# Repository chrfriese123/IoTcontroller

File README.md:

# ESP8266 based controller for smart home applications
## Introduction
The target is to setup a versatile smart home system. Home Assistant (www.home-assistant.io) running on a Raspberry Pi is used as open-source platform to integrate various devices from multiple brands. Especially to control lights and covers a system should comply with four requirements: 
- can be directly connected to the wall switches (limited size)
- is not linked to a specific supplier (open source)
- has direct connection to the host controller without the need of a bridge (Wifi)
- has low cost

As a solution a system based on an ESP8266 chip operated with Tasmota (tasmota.github.io) seems suitable. 

## Implementation
The schematic and layout of the PCB was implemented with the free version of KiCAD. The key elements are inspired by proven designs and combined in a minimalistic way on the PCB.

### Power supply
For the power supply, two step-down converters are used. The first one to convert from 230VAC to 5VDC. This is mainly used to operate the relays. The second conversion is by a simple LDO from 5VDC to 3.3VDC to operate the ESP8266.

### ESP8266 contoller
As controller an ESP8266 module was used to operate up to two relays, enable two external switches as input and a I2C communication to external devices.

For the operation and programming of the ESP8266 certain pins need to be pulled high. Two miniaturized switches are included to reset the device or get into programming mode.

### Relays
Two relay channels are implemented to allow an operation of one cover or two lights with the system. As option, an LED can be activated to indicate the state of the relay.

### Layout
The layout is defined by the used wall switch program. Two screw holes need to be considered, front size has a reduced size and limited height.

To reduce the risk, high voltage line are placed on the backside, covered by components. Low voltage and signal lines are placed as much as possible of the frontside. 

### ESP8266 contoller
As controller an ESP8266 module was used to operate up to two relays, enable two external switches as input and a I2C communication to external devices.

For the operation and programming of the ESP8266 certain pins need to be pulled high. Two miniaturized switches are included to reset the device or get into programming mode.

### Relays
Two relay channels are implemented to allow an operation of one cover or two lights with the system. As option, an LED can be activated to indicate the state of the relay.

### Layout
The layout is defined by the used wall switch program. Two screw holes need to be considered, front size has a reduced size and limited height.
To reduce the risk, high voltage line are placed on the backside, covered by components. Low voltage and signal lines are placed as much as possible of the frontside. 

### Firmware
To operate the ESP system, the open-source firmware Tasmota is used (https://tasmota.github.io/docs/). For the majority of the controllers the standard firmware is suitable. Although some cases need a dedicated version to enable operation of RGB LED stripes, read specific I2C sensors or read the power & water meters.

### Preparation
The bare PCB is produced by a Chinese manufacturer. Assembly is done manually, first the SMD components and the ESP8266 module. Then a system check and programming is performed. Finally, the through hole components are soldered.

## Summary
Currently 24 of theses IoT controller are installed and running as
- Cover switches
- Light switches (bulbs and RGB LEDs)
- 3D printer controller
- Power & water metering
- Valve controller for gardening
- Environmental sensors
  
The overall failure rate of the system is low and not except for one ESP8266 module breakdown not linked to the design. The cost of one module is about 10€. To conclude, the initial targets are fulfilled, and the system is constantly extended.

### Next steps
As an improved version the transition to ESP32 would be helpful to increase the number of available GPIOs. Another limitation is that the relays can only handle 7A max current, which might be critical for some use-cases

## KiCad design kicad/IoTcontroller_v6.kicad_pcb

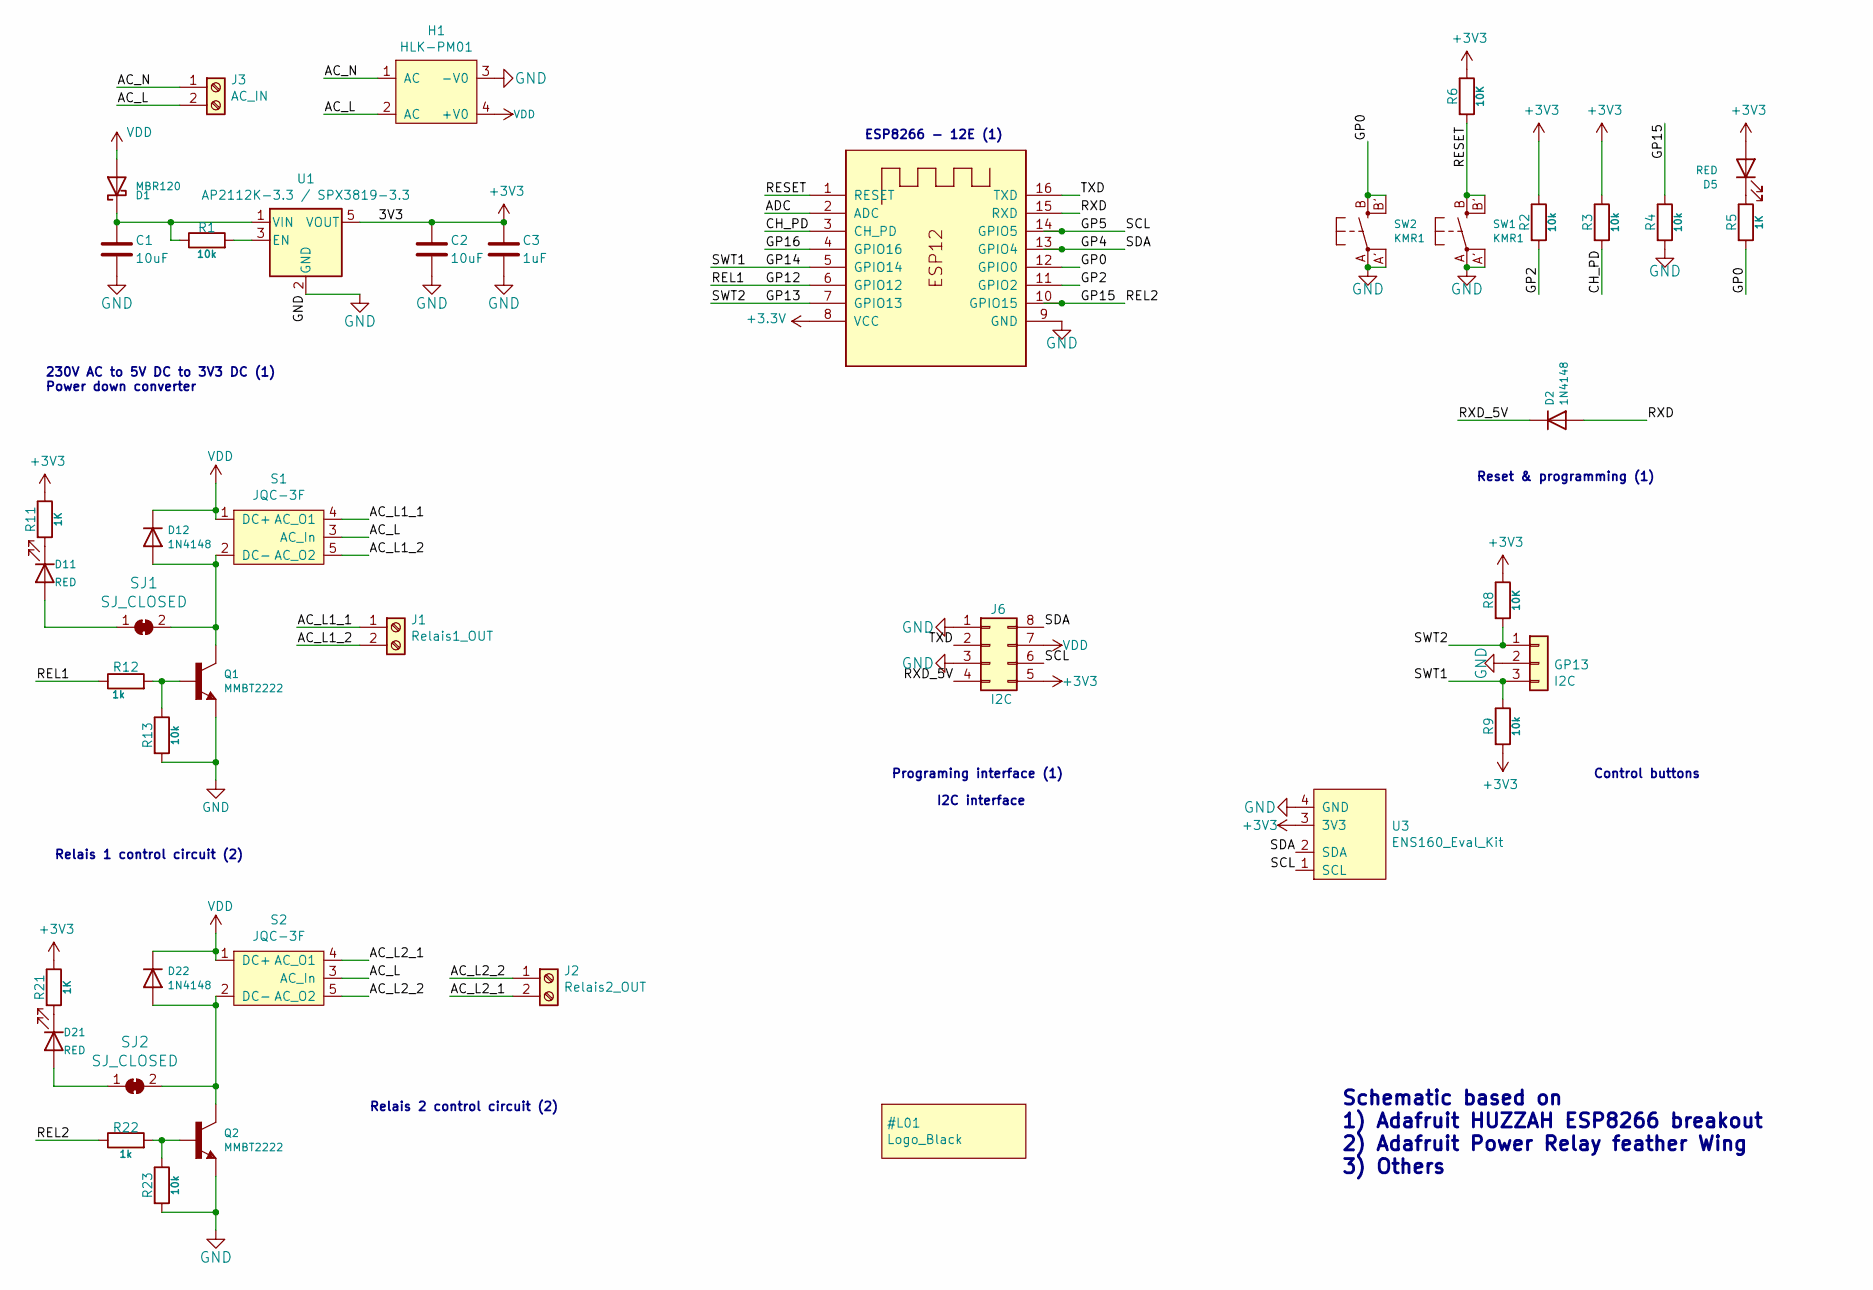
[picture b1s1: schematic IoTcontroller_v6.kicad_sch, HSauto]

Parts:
C1, C2: 10uF; C_0805_2012Metric
C3: 1uF; C_0805_2012Metric
D1: MBR120; D_SOD-123
D2, D12, D22: 1N4148; D_SOD-323
D5, D11, D21: RED; LED_0805_2012Metric
GP13: I2C; PinHeader_1x03_P2.54mm_Vertical
H1: HLK-PM01
J1: Relais1_OUT; PTSA1,5-2-3,5-Z
J2: Relais2_OUT; PTSA1,5-2-3,5-Z
J3: AC_IN; PTSA1,5-2-3,5-Z
J6: I2C; PinHeader_2x04_P2.54mm_Vertical
Q1, Q2: MMBT2222; SOT-23
R1, R2, R3, R4, R9, R13, R23: 10k; R_0805_2012Metric
R5, R11, R21: 1K; R_0805_2012Metric
R6, R8: 10K; R_0805_2012Metric
R12, R22: 1k; R_0805_2012Metric
S1, S2: JQC-3F
SJ1, SJ2: SJ_CLOSED; SolderJumper-2_P1.3mm_Bridged_RoundedPad1.0x1.5mm
SW1, SW2: KMR1; BTN_KMR2_4.6X2.8
U1: AP2112K-3.3 / SPX3819-3.3; SOT-23-5
U3: ENS160_Eval_Kit; ScioSense_ENS16x_EvalKit
X1: ESP-12

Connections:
/AC_L: H1.2 (AC), J3.2, S1.3 (AC_In), S2.3 (AC_In)
/AC_L1_1: J1.1, S1.4 (AC_O1)
/AC_L1_2: J1.2, S1.5 (AC_O2)
/AC_L2_1: J2.2, S2.4 (AC_O1)
/AC_L2_2: J2.1, S2.5 (AC_O2)
/AC_N: H1.1 (AC), J3.1
/ADC: X1.2 (ADC)
/CH_PD: R3.2, X1.3 (CH_PD)
/GP0: R5.2, SW2.B (S), SW2.B' (S1), X1.12 (GPIO0)
/GP2: R2.2, X1.11 (GPIO2)
/GP4: J6.8, U3.2 (SDA), X1.13 (GPIO4)
/GP5: J6.6, U3.1 (SCL), X1.14 (GPIO5)
/GP12: R12.1, X1.6 (GPIO12)
/GP13: GP13.1, R8.2, X1.7 (GPIO13)
/GP14: GP13.3, R9.1, X1.5 (GPIO14)
/GP15: R4.1, R22.1, X1.10 (GPIO15)
/GP16: X1.4 (GPIO16)
/RESET: R6.2, SW1.B (S), SW1.B' (S1), X1.1 (RESET)
/RXD: D2.2 (A), X1.15 (RXD)
/RXD_5V: D2.1 (K), J6.4
/TXD: J6.2, X1.16 (TXD)
GND: C1.2, C2.2, C3.2, GP13.2, H1.3 (-V0), J6.1, J6.3, Q1.2 (E), Q2.2 (E), R4.2, R13.2, R23.2, SW1.A, SW1.A' (P1), SW2.A, SW2.A' (P1), U1.2 (GND), U3.4 (GND), X1.9 (GND)
unnamed: C1.1, D1.1 (K), R1.1, U1.1 (VIN)
unnamed: D5.1 (K), R5.1
unnamed: D11.2 (A), SJ1.1 (A)
unnamed: D11.1 (K), R11.2
unnamed: D12.2 (A), Q1.3 (C), S1.2 (DC-), SJ1.2 (B)
unnamed: D21.2 (A), SJ2.1 (A)
unnamed: D21.1 (K), R21.2
unnamed: D22.2 (A), Q2.3 (C), S2.2 (DC-), SJ2.2 (B)
unnamed: Q1.1 (B), R12.2, R13.1
unnamed: Q2.1 (B), R22.2, R23.1
unnamed: R1.2, U1.3 (EN)
VDD: D1.2 (A), D12.1 (K), D22.1 (K), H1.4 (+V0), J6.7, S1.1 (DC+), S2.1 (DC+)

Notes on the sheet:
Control buttons
230V AC to 5V DC to 3V3 DC (1) Power down converter
Relais 2 control circuit (2)
Relais 1 control circuit (2)
ESP8266 - 12E (1)
I2C interface
Reset & programming (1)
Programing interface (1)
Schematic based on 1) Adafruit HUZZAH ESP8266 breakout 2) Adafruit Power Relay feather Wing 3) Others

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
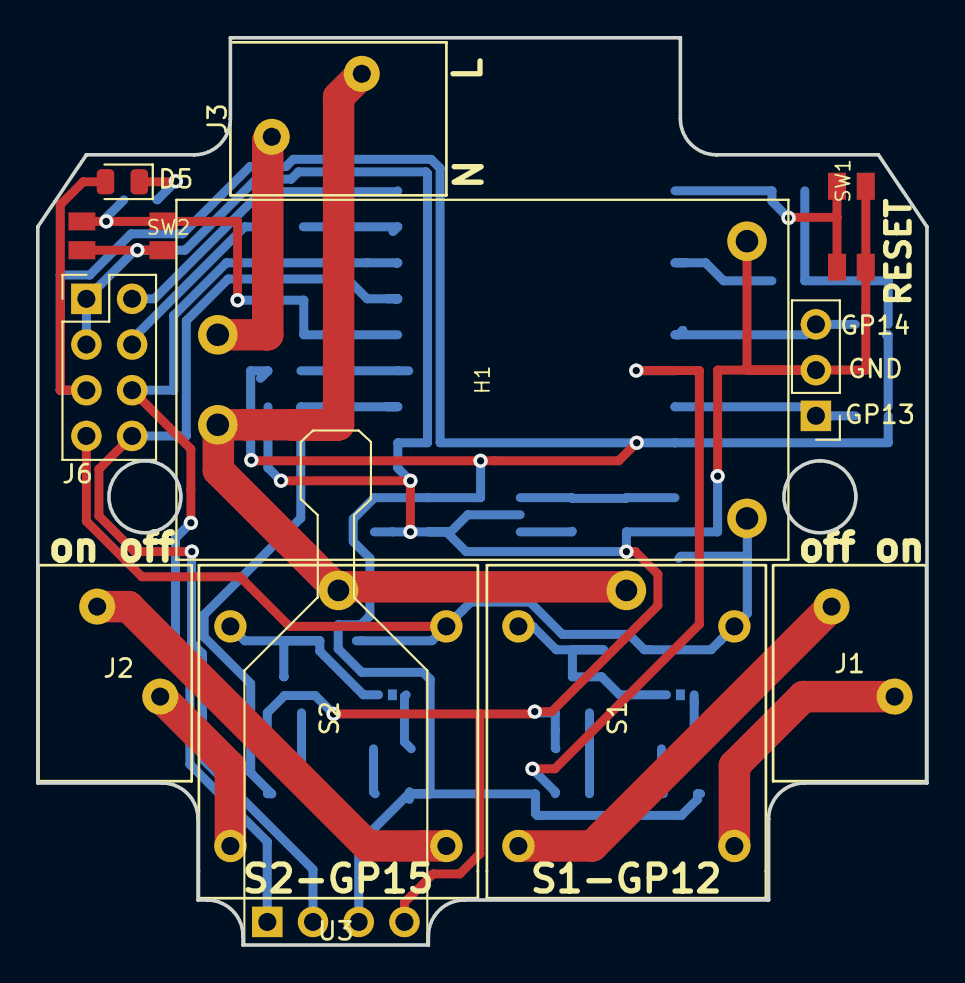
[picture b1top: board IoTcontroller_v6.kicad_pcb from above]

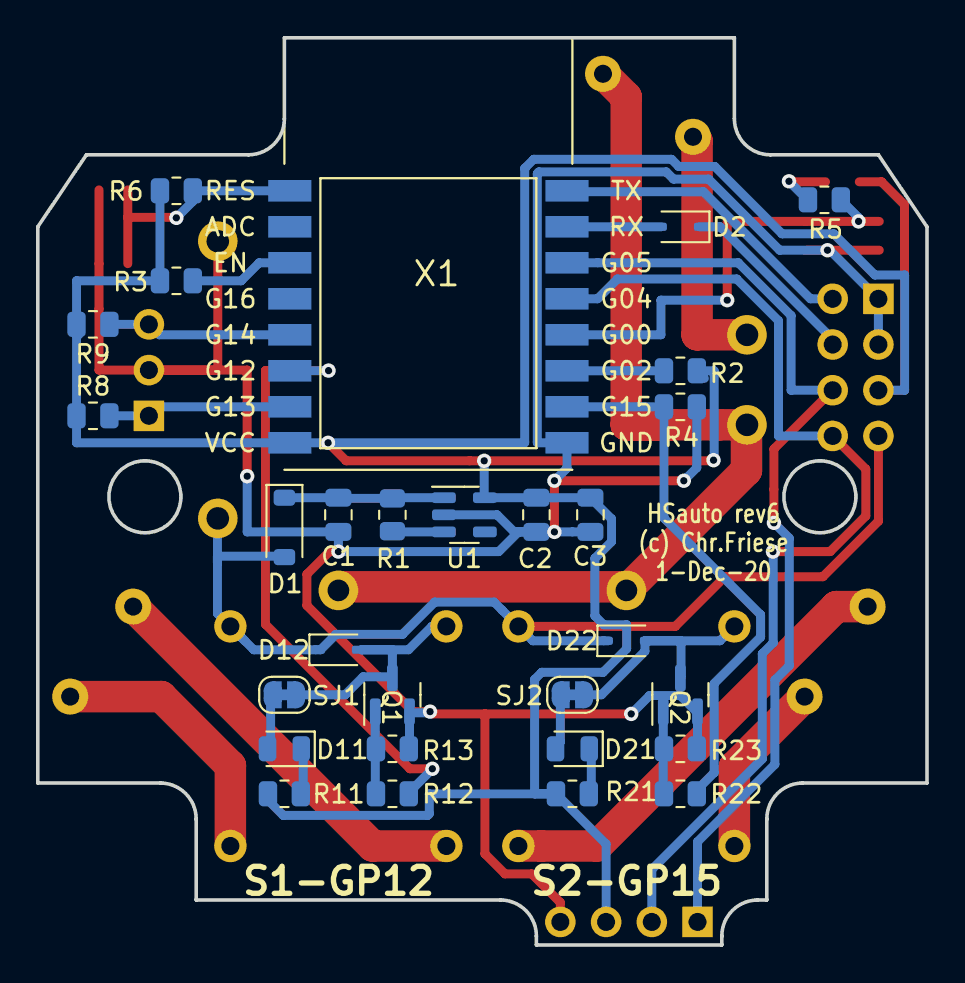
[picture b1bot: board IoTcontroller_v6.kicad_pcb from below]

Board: 2 copper layers, 49.4 x 50.4 mm, 41 parts (29 on the bottom side), 33 nets.

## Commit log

2024-03-09 Image size adjusted
2024-03-09 Update README.md
    Add link to Tasmota
